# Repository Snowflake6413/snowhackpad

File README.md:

# snowhackpad

I created this Hackpad because I wanted to explore hardware and learn how to use different software.

## What softwared I learned throughout this project
* Fusion360
* Python
* KiCAD
## Challenges
* Firmware. I didnt know about Python much and KMK. I read some docs and looked some example. I wrote my firmware and I hope for the best.
* Fusion360 : It's a really new software for me. I had some problems but in the end, the result looks promising.

# CAD
PCB | Top Case | Bottom Case
:----------------------:|:----------------------:|:----------------------:
 |  | 

# Schematics/PCB
PCB | Schematics |
:----------------------:|:----------------------:
 | 

# Bill of Materials
* 1x Seeed Studio XIAO RP2040
* 4x MX-Style switches
* 4x Blank DSA keycaps
* 1x 0.91 inch OLED display
* 1x EC11 Rotary encoder
* 3x SK6812 MINI-E LEDs
* 4x M3x16mm screws

## Final notes
* I really hoped this gets approved! I worked really hard on this. (Aprox 3 days)
* I wish Fusion360 was simple and easier.
* This is my first blueprint project!

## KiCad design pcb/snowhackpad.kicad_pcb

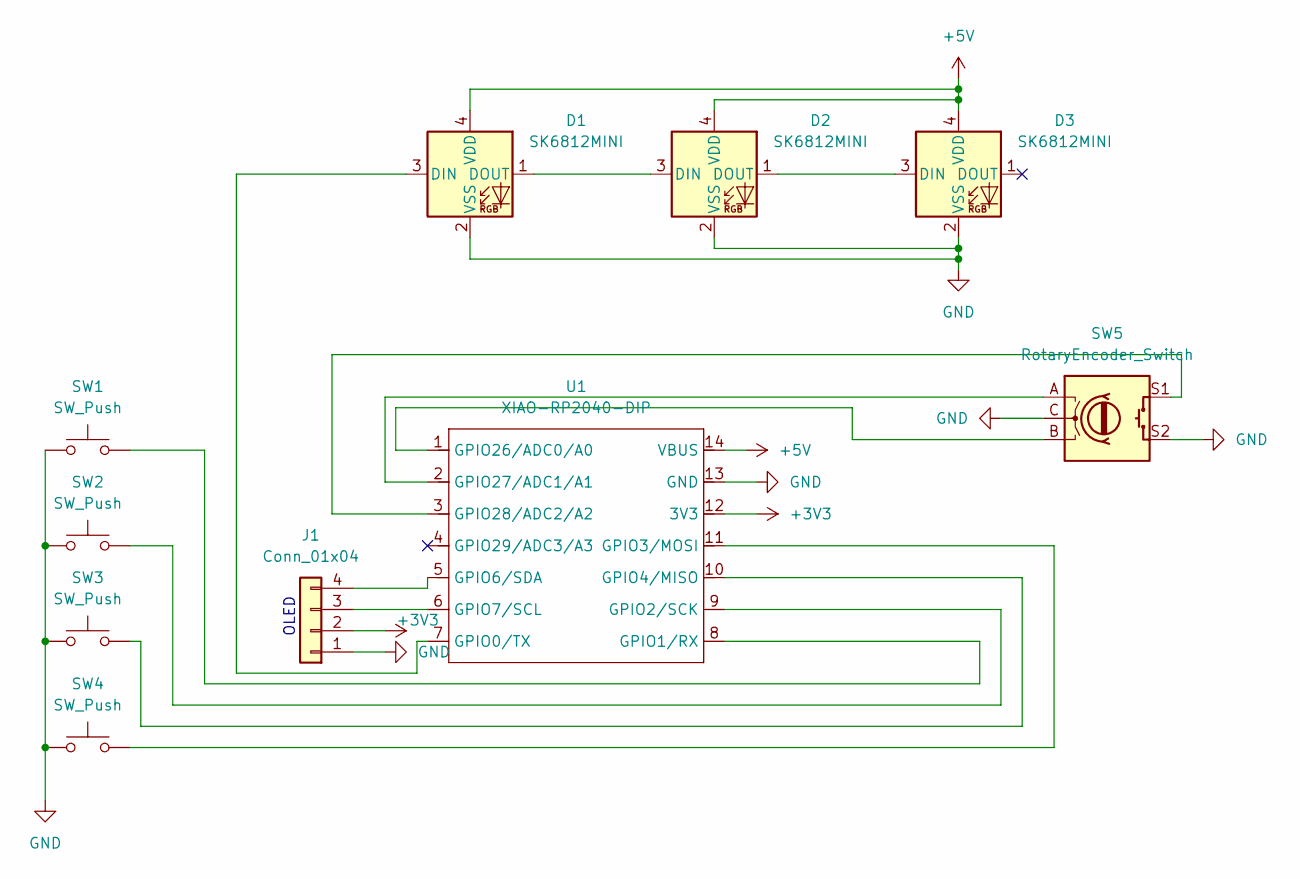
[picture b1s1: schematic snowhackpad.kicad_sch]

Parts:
D1, D2, D3: SK6812MINI; LED_SK6812MINI_PLCC4_3.5x3.5mm_P1.75mm
J1: Conn_01x04; SSD1306-0.91-OLED-4pin-128x32
SW1, SW2, SW3, SW4: SW_Push; SW_Cherry_MX_1.00u_PCB
SW5: RotaryEncoder_Switch; RotaryEncoder_Alps_EC11E-Switch_Vertical_H20mm
U1: XIAO-RP2040-DIP

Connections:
+3V3: J1.2, U1.12 (3V3)
+5V: D1.4 (VDD), D2.4 (VDD), D3.4 (VDD), U1.14 (VBUS)
GND: D1.2 (VSS), D2.2 (VSS), D3.2 (VSS), J1.1, SW1.1, SW2.1, SW3.1, SW4.1, SW5.C, SW5.S2, U1.13 (GND)
unnamed: D1.3 (DIN), U1.7 (GPIO0/TX)
unnamed: D1.1 (DOUT), D2.3 (DIN)
unnamed: D2.1 (DOUT), D3.3 (DIN)
unnamed: J1.3, U1.6 (GPIO7/SCL)
unnamed: J1.4, U1.5 (GPIO6/SDA)
unnamed: SW1.2, U1.8 (GPIO1/RX)
unnamed: SW2.2, U1.9 (GPIO2/SCK)
unnamed: SW4.2, U1.11 (GPIO3/MOSI)
unnamed: SW3.2, U1.10 (GPIO4/MISO)
unnamed: SW5.B, U1.1 (GPIO26/ADC0/A0)
unnamed: SW5.A, U1.2 (GPIO27/ADC1/A1)
unnamed: SW5.S1, U1.3 (GPIO28/ADC2/A2)

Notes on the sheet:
OLED

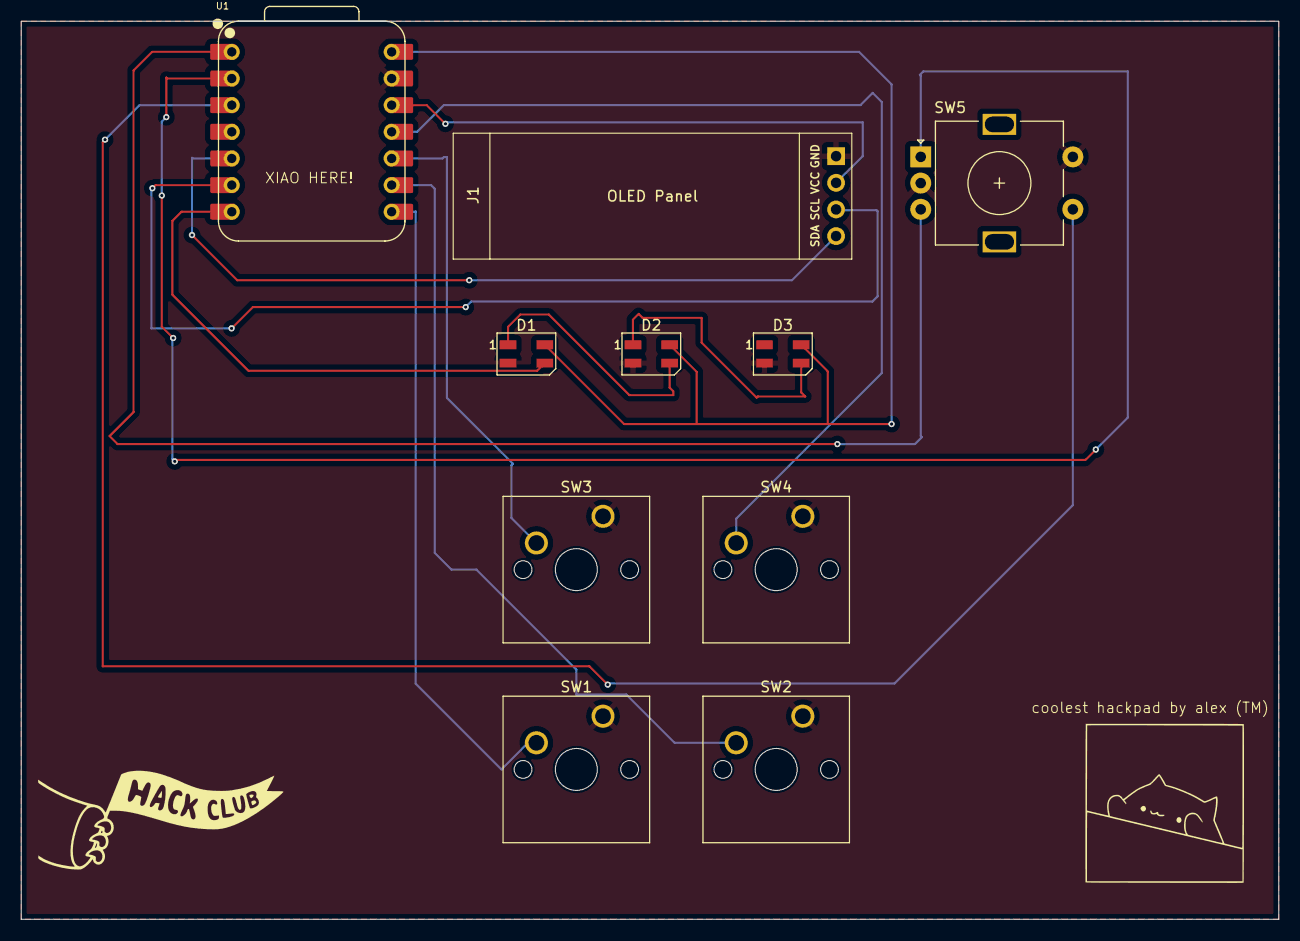
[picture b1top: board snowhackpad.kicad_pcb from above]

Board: 2 copper layers, 119.9 x 85.6 mm, 10 parts (0 on the bottom side), 15 nets.

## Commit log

2025-11-26 Feat: Add RGB support
2025-11-26 Add: CAD and PCB Files. Update: Readme with more info
2025-11-26 Add: Snowhackpad model files + PCB, Top and Bottom case model files Update: README with more information
2025-11-26 Update: Readme with Final notes
2025-11-26 Update: Update Kicad PCB
